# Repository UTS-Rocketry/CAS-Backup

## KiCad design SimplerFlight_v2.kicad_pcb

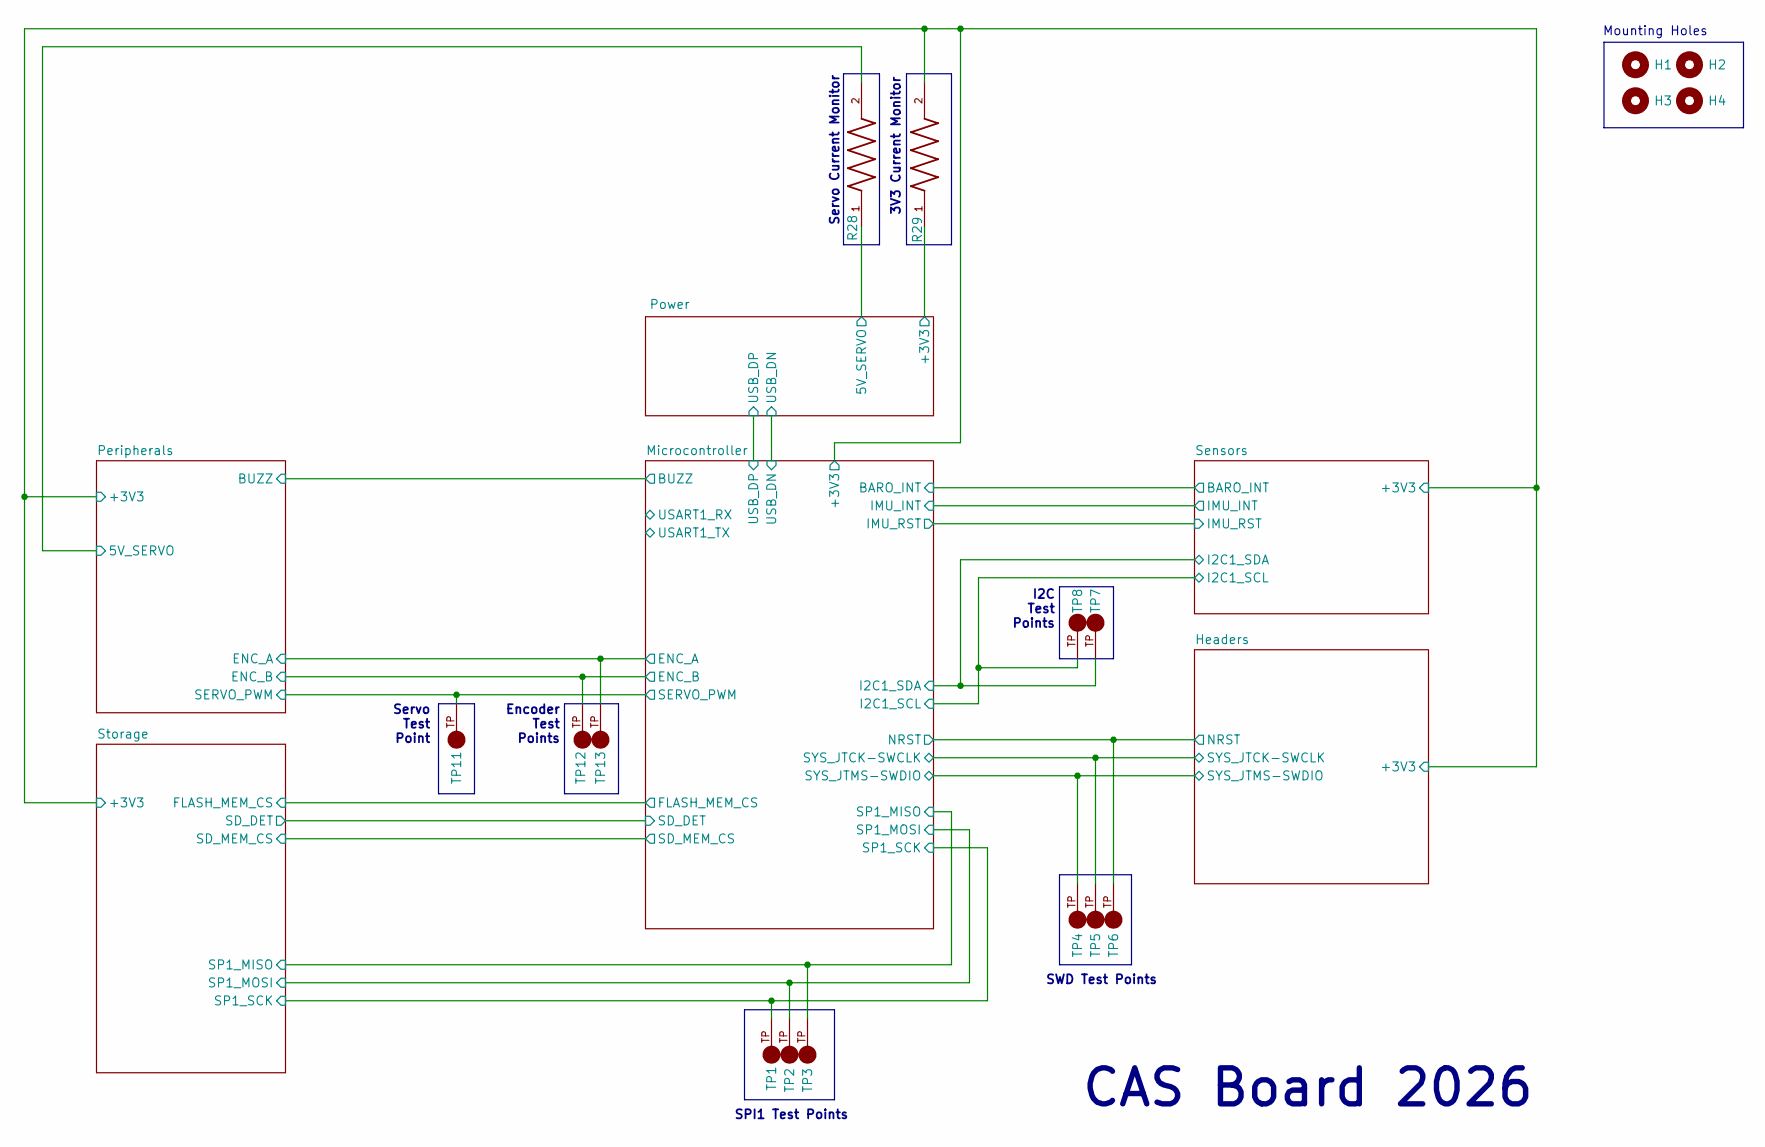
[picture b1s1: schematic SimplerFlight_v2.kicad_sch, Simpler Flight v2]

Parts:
H1, H2, H3, H4: MountingHole; MountingHole_3.2mm_M3
R28, R29: CSRN2512FKR500; RESC6331X70N
TP1, TP2, TP3, TP4, TP5, TP6, TP7, TP8, TP11, TP12, TP13: 5016; KEYSTONE_5016; PARTREV D

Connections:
/Headers/+3V3: R29.2; also elsewhere on the board
/Microcontroller/12C1_SCL: TP8.TP; also elsewhere on the board
/Microcontroller/12C1_SDA: TP7.TP; also elsewhere on the board
/Microcontroller/SPI1_MISO: TP3.TP; also elsewhere on the board
/Microcontroller/SPI1_MOSI: TP2.TP; also elsewhere on the board
/Microcontroller/SPI1_SCK: TP1.TP; also elsewhere on the board
/Peripherals/5V_SERVO: R28.2; also elsewhere on the board
/Power/3V3: R29.1; also elsewhere on the board
/Power/5V_SERVO: R28.1; also elsewhere on the board

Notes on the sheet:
SWD Test Points
3V3 Current Monitor
I2C Test Points
Servo Test Point
SPI1 Test Points
Servo Current Monitor
CAS Board 2026
Mounting Holes
Encoder Test Points

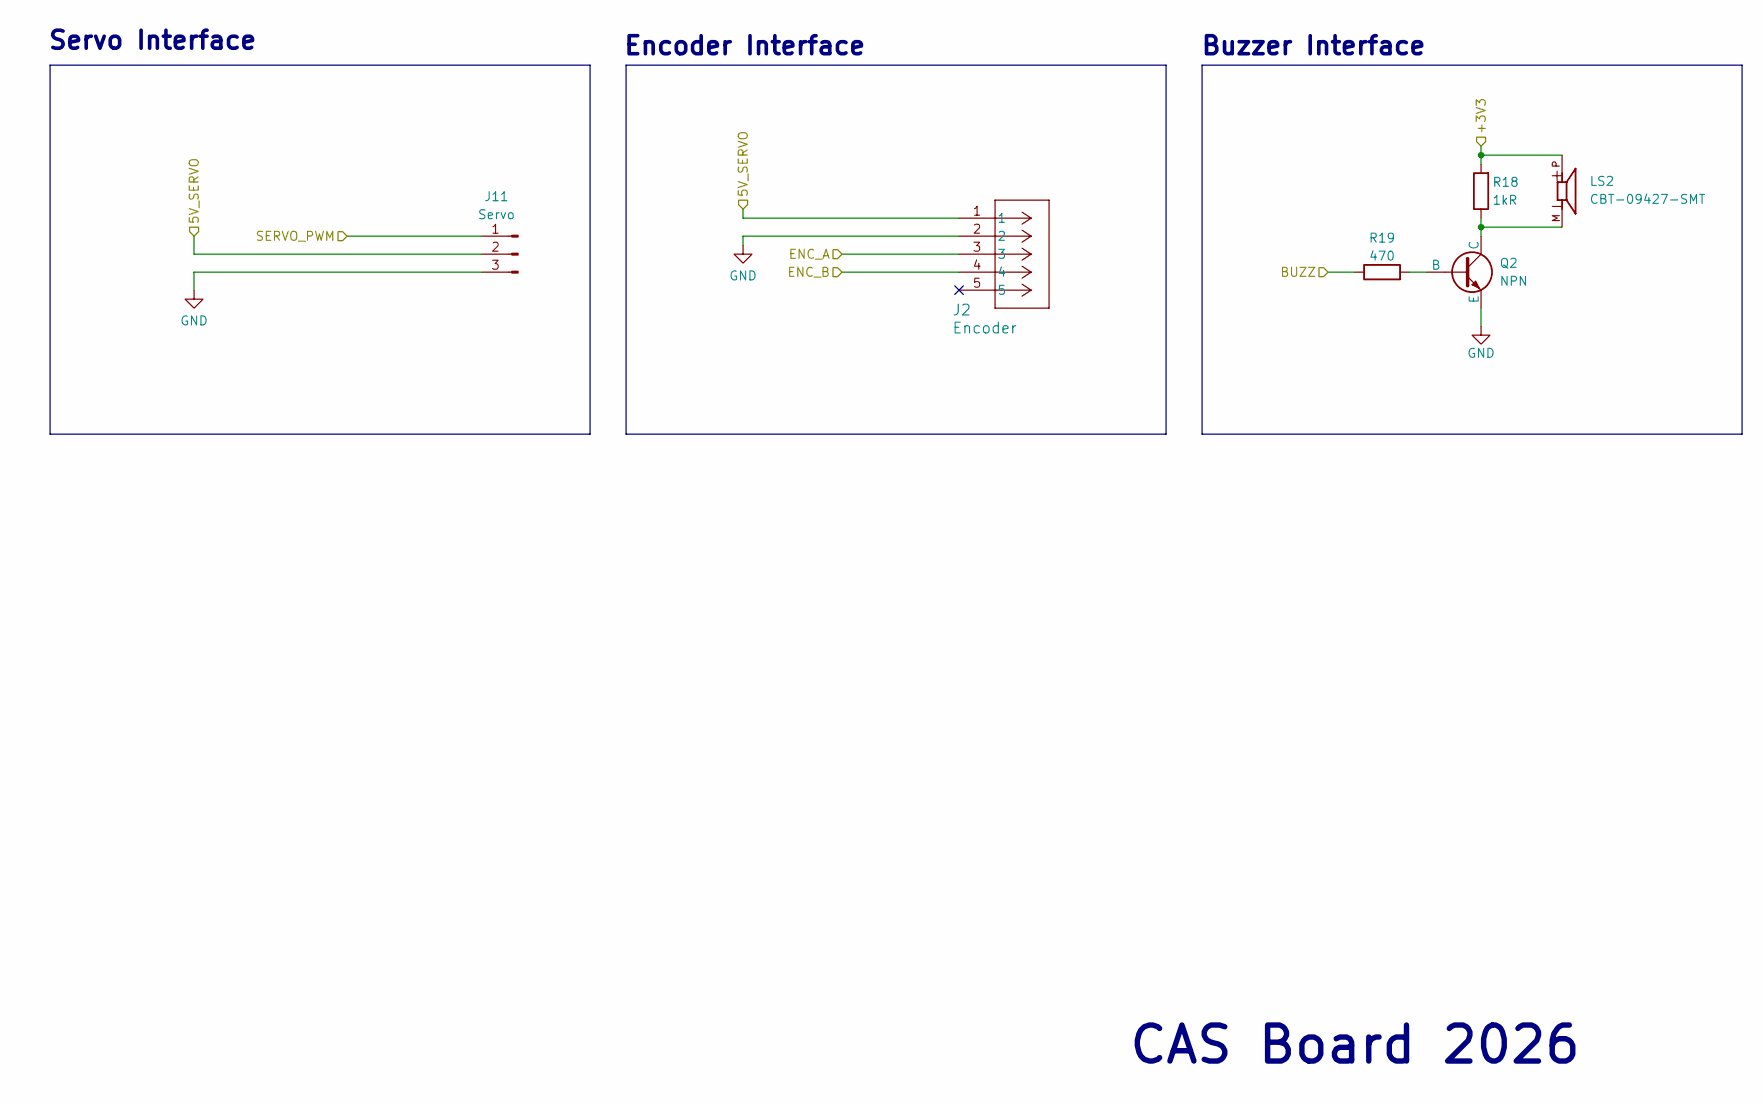
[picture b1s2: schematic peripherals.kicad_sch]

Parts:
J2: Encoder; CONN_S05B-PASK-2_JST
J11: Servo; PinHeader_1x03_P2.54mm_Vertical
LS2: CBT-09427-SMT; CUI_CBT-09427-SMT
Q2: NPN; SSOT3_3X1P5_ONS
R18: 1kR; R_0805_2012Metric_Pad1.20x1.40mm_HandSolder
R19: 470; R_0805_2012Metric_Pad1.20x1.40mm_HandSolder

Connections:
/Headers/+3V3: LS2.P, R18.2; also elsewhere on the board
/Microcontroller/BUZZ: R19.1; also elsewhere on the board
/Microcontroller/ENC_A: J2.3; also elsewhere on the board
/Microcontroller/ENC_B: J2.4; also elsewhere on the board
/Microcontroller/SERVO_PWM: J11.1; also elsewhere on the board
/Peripherals/5V_SERVO: J2.1, J11.2; also elsewhere on the board
GND: J2.2, J11.3, Q2.3 (E); also elsewhere on the board
unnamed: Q2.2 (B), R19.2
unnamed: LS2.M, Q2.1 (C), R18.1

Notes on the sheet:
Encoder Interface
CAS Board 2026
Servo Interface
Buzzer Interface

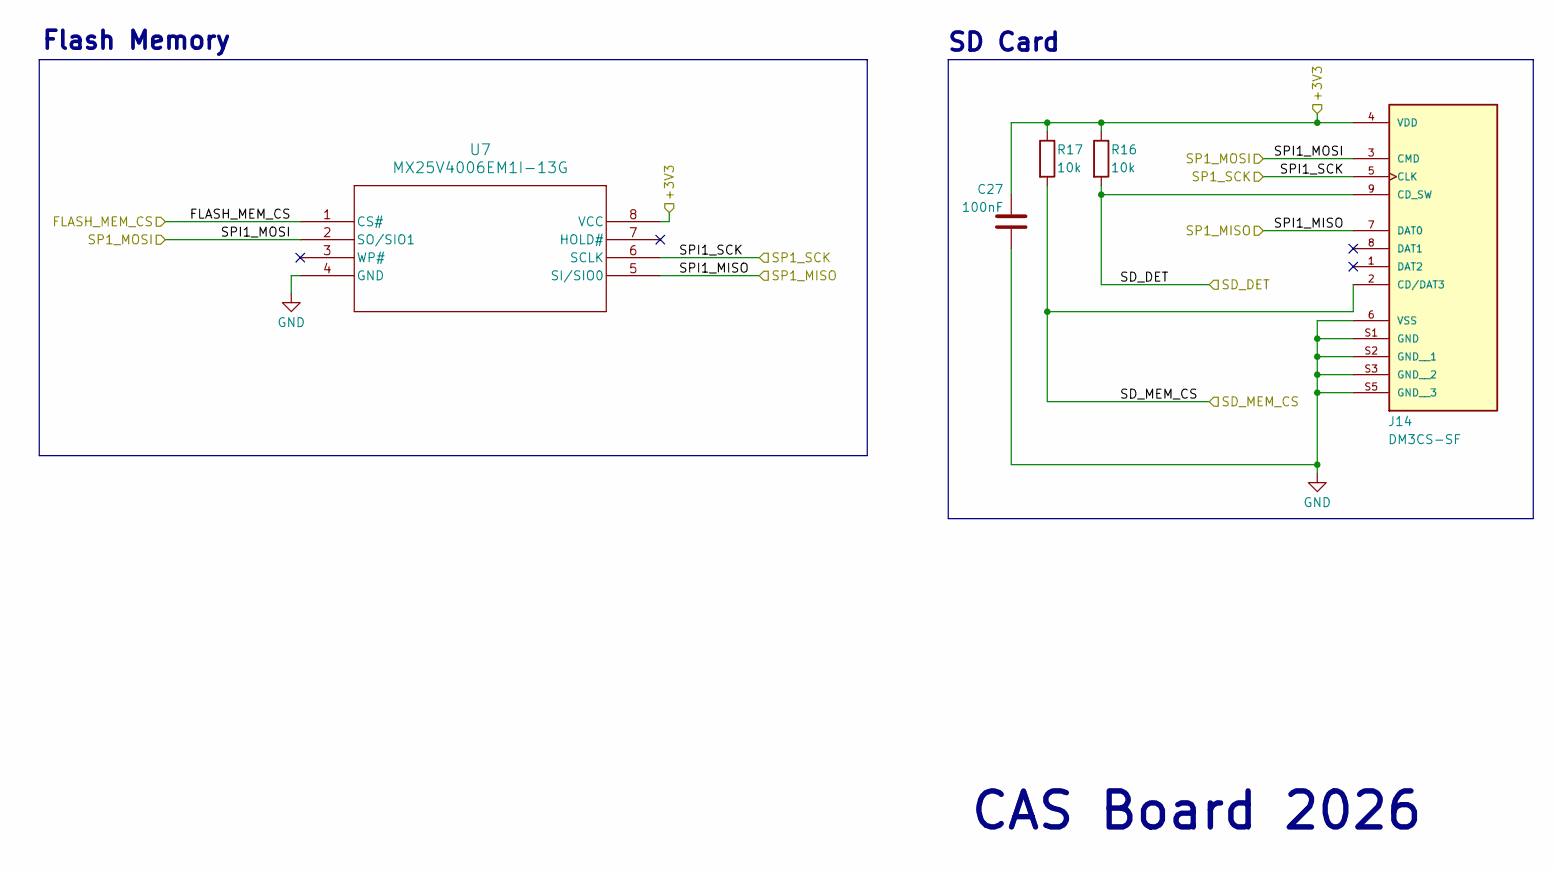
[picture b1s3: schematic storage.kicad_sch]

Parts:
C27: 100nF; C_0805_2012Metric_Pad1.18x1.45mm_HandSolder
J14: DM3CS-SF; HRS_DM3CS-SF; PARTREV n/a
R16, R17: 10k; R_0805_2012Metric_Pad1.20x1.40mm_HandSolder
U7: MX25V4006EM1I-13G; SOP8_150_MAC

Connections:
/Headers/+3V3: C27.1, J14.4 (VDD), R16.1, R17.1, U7.8 (VCC); also elsewhere on the board
/Microcontroller/FLASH_MEM_CS: U7.1 (CS#); also elsewhere on the board
/Microcontroller/SD_DET: J14.9 (CD_SW), R16.2; also elsewhere on the board
/Microcontroller/SD_MEM_CS: J14.2 (CD/DAT3), R17.2; also elsewhere on the board
/Microcontroller/SPI1_MISO: J14.7 (DAT0), U7.5 (SI/SIO0); also elsewhere on the board
/Microcontroller/SPI1_MOSI: J14.3 (CMD), U7.2 (SO/SIO1); also elsewhere on the board
/Microcontroller/SPI1_SCK: J14.5 (CLK), U7.6 (SCLK); also elsewhere on the board
GND: C27.2, J14.6 (VSS), J14.S1 (GND), J14.S2 (GND__1), J14.S3 (GND__2), J14.S5 (GND__3), U7.4 (GND); also elsewhere on the board

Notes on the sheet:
Flash Memory
SD Card
CAS Board 2026

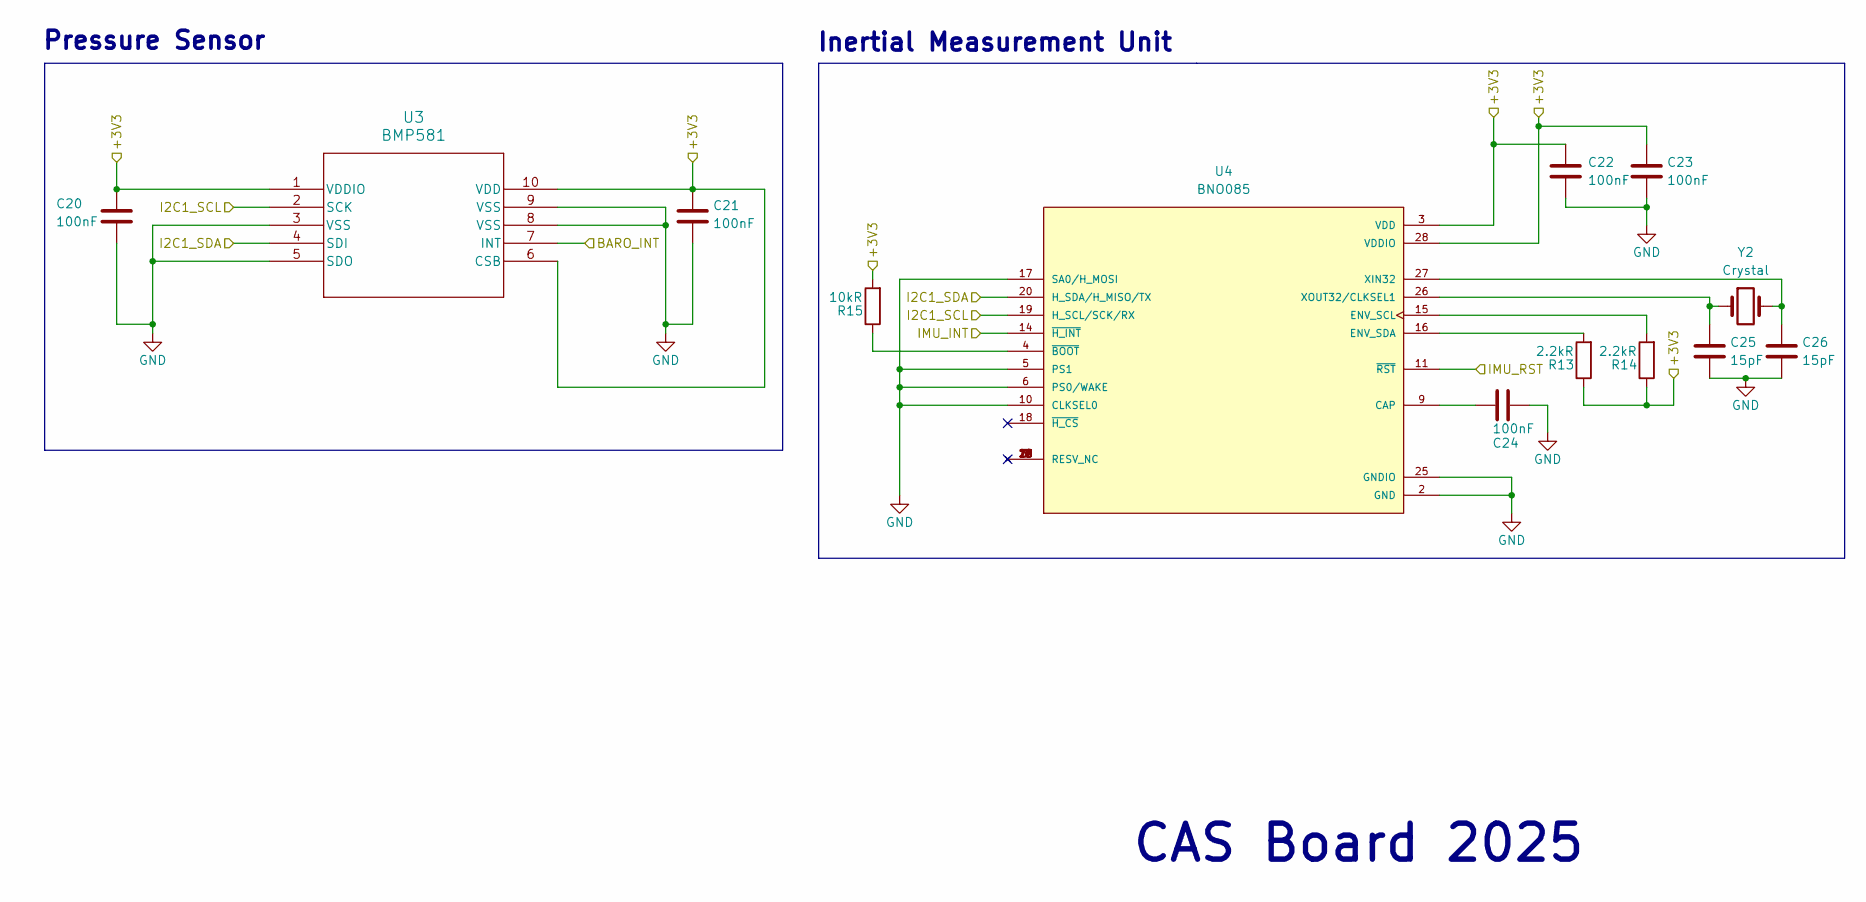
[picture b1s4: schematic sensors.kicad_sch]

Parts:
C20, C21, C22, C23, C24: 100nF; C_0805_2012Metric
C25, C26: 15pF; C_0805_2012Metric
R13, R14: 2.2kR; R_0805_2012Metric_Pad1.20x1.40mm_HandSolder
R15: 10kR; R_0805_2012Metric_Pad1.20x1.40mm_HandSolder
U3: BMP581; QFN10_BMP581_BOS
U4: BNO085; IC_BNO085; PARTREV v1.17
Y2: Crystal; Crystal_SMD_0603-2Pin_6.0x3.5mm_HandSoldering

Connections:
/Headers/+3V3: C20.1, C21.1, C22.1, C23.1, R13.1, R14.1, R15.2, U3.1 (VDDIO), U3.6 (CSB), U3.10 (VDD), U4.3 (VDD), U4.28 (VDDIO); also elsewhere on the board
/Microcontroller/12C1_SCL: U3.2 (SCK), U4.19 (H_SCL/SCK/RX); also elsewhere on the board
/Microcontroller/12C1_SDA: U3.4 (SDI), U4.20 (H_SDA/H_MISO/TX); also elsewhere on the board
/Microcontroller/BARO_INT: U3.7 (INT); also elsewhere on the board
/Microcontroller/IMU_INT: U4.14 (~H_INT); also elsewhere on the board
/Microcontroller/IMU_RST: U4.11 (~RST); also elsewhere on the board
GND: C20.2, C21.2, C22.2, C23.2, C24.1, C25.2, C26.2, U3.3 (VSS), U3.5 (SDO), U3.8 (VSS), U3.9 (VSS), U4.2 (GND), U4.5 (PS1), U4.6 (PS0/WAKE), U4.10 (CLKSEL0), U4.17 (SA0/H_MOSI), U4.25 (GNDIO); also elsewhere on the board
unnamed: C24.2, U4.9 (CAP)
unnamed: R14.2, U4.15 (ENV_SCL)
unnamed: R13.2, U4.16 (ENV_SDA)
unnamed: C26.1, U4.27 (XIN32), Y2.2
unnamed: C25.1, U4.26 (XOUT32/CLKSEL1), Y2.1
unnamed: R15.1, U4.4 (~BOOT)

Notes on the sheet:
CAS Board 2025
Inertial Measurement Unit
Pressure Sensor

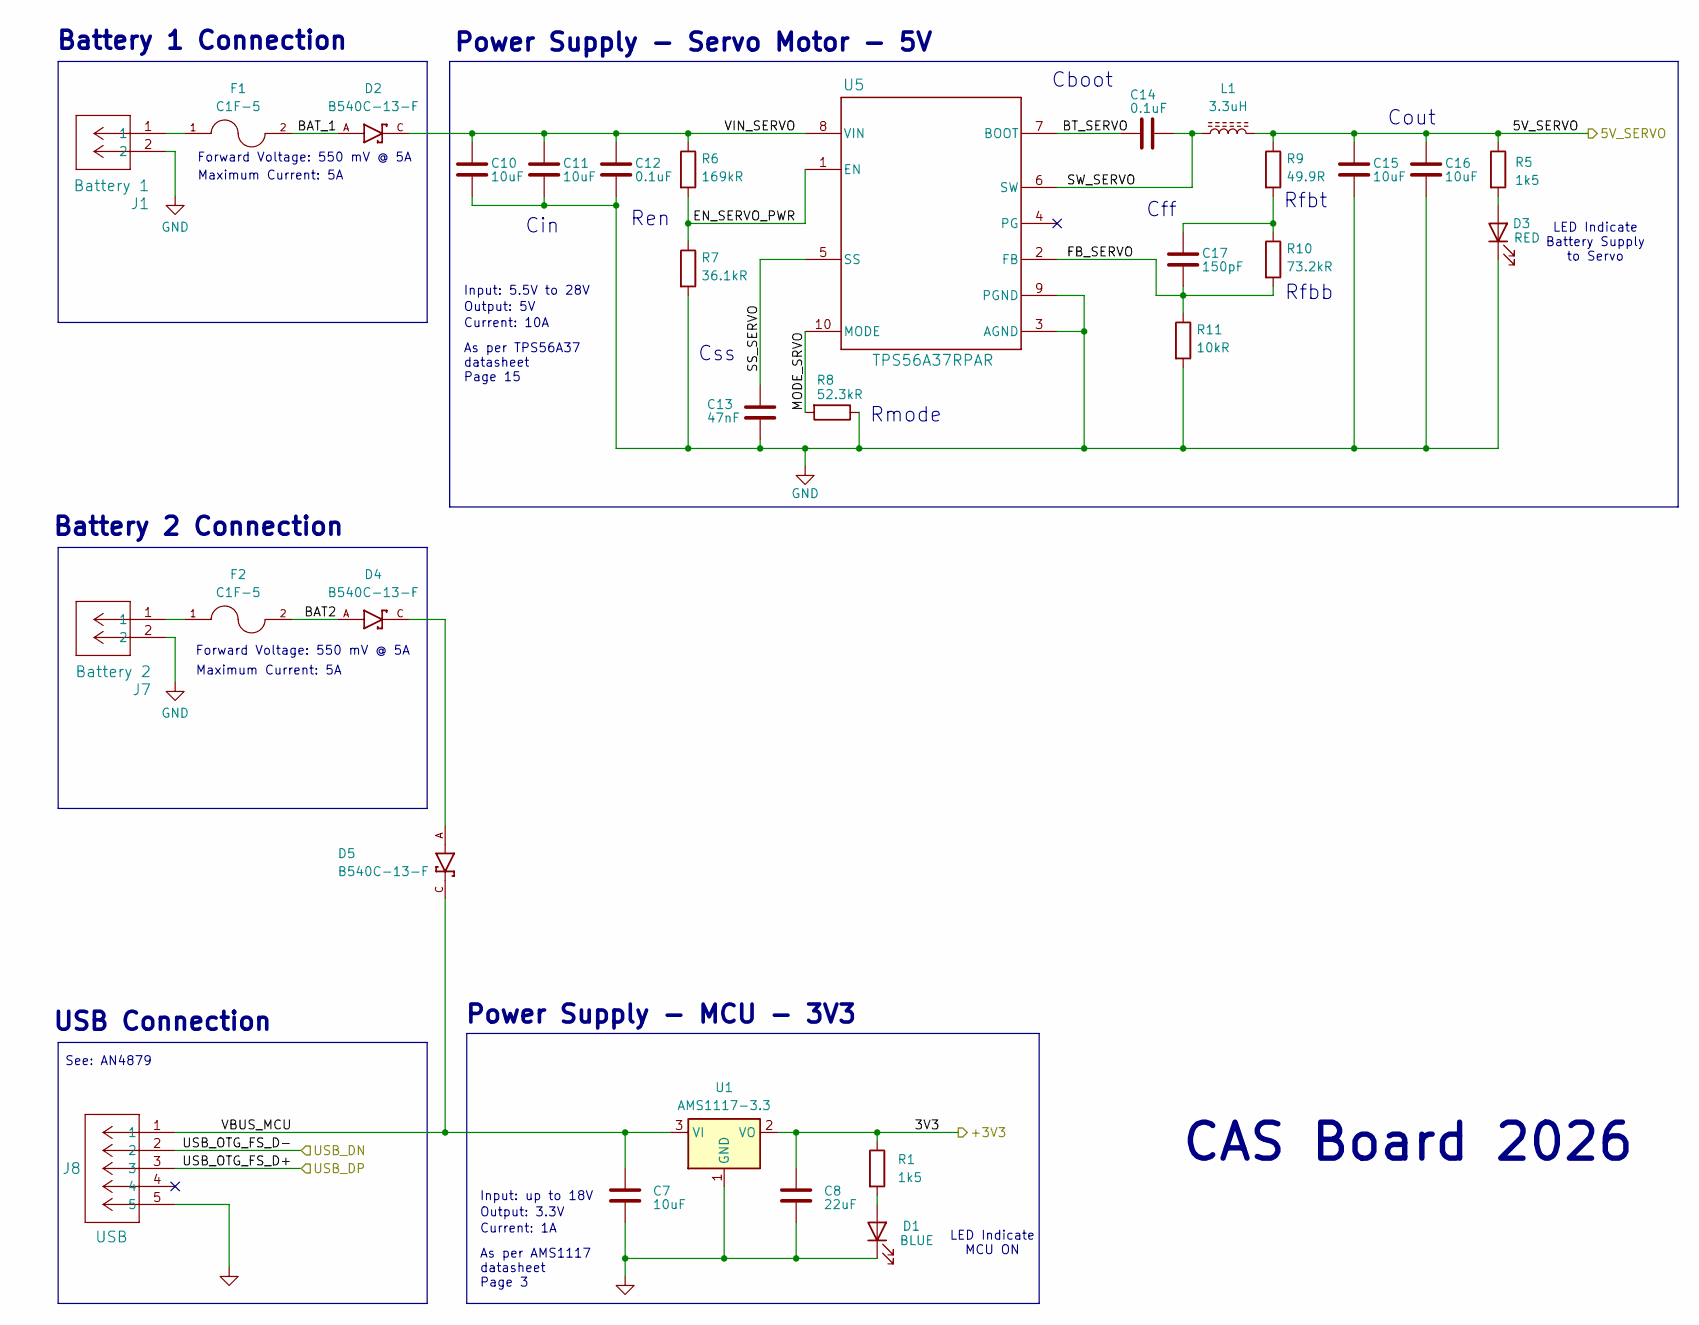
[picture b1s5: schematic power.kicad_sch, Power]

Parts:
C7, C10, C11, C15, C16: 10uF; C_0805_2012Metric
C8: 22uF; C_0805_2012Metric
C12, C14: 0.1uF; C_0805_2012Metric
C13: 47nF; C_0805_2012Metric
C17: 150pF; C_0805_2012Metric
D1: BLUE; LED_0805_2012Metric
D2, D4, D5: B540C-13-F; DIOM6959X245N; PARTREV V1.0
D3: RED; LED_0805_2012Metric
F1, F2: C1F-5; FUSC3215X83N; PARTREV Jan2019
J1: Battery 1; CONN_SD-5566-002_02_MOL
J7: Battery 2; CONN_SD-5566-002_02_MOL
J8: USB; CON00317_5_MOL
L1: 3.3uH; L_0805_2012Metric_Pad1.05x1.20mm_HandSolder
R1, R5: 1k5; C_0805_2012Metric
R6: 169kR; C_0805_2012Metric
R7: 36.1kR; C_0805_2012Metric
R8: 52.3kR; C_0805_2012Metric
R9: 49.9R; C_0805_2012Metric
R10: 73.2kR; C_0805_2012Metric
R11: 10kR; C_0805_2012Metric
U1: AMS1117-3.3; SOT-223-3_TabPin2
U5: TPS56A37RPAR; RPA0010A-MFG

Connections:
/Microcontroller/USB_OTG_FS_D+: J8.3; also elsewhere on the board
/Microcontroller/USB_OTG_FS_D-: J8.2; also elsewhere on the board
/Power/3V3: C8.1, R1.1, U1.2 (VO); also elsewhere on the board
/Power/5V_SERVO: C15.1, C16.1, L1.2, R5.1, R9.1; also elsewhere on the board
/Power/BAT2: D4.A, F2.2
/Power/BAT_1: D2.A, F1.2
/Power/BT_SERVO: C14.1, U5.7 (BOOT)
/Power/EN_SERVO_PWR: R6.2, R7.1, U5.1 (EN)
/Power/FB_SERVO: C17.2, R10.2, R11.1, U5.2 (FB)
/Power/MODE_SRVO: R8.2, U5.10 (MODE)
/Power/SS_SERVO: C13.1, U5.5 (SS)
/Power/SW_SERVO: C14.2, L1.1, U5.6 (SW)
/Power/VBUS_MCU: C7.1, D5.C, J8.1, U1.3 (VI)
/Power/VIN_SERVO: C10.1, C11.1, C12.1, D2.C, R6.1, U5.8 (VIN)
GND: C7.2, C8.2, C10.2, C11.2, C12.2, C13.2, C15.2, C16.2, D1.1 (K), D3.1 (K), J1.2, J7.2, J8.5, R7.2, R8.1, R11.2, U1.1 (GND), U5.3 (AGND), U5.9 (PGND); also elsewhere on the board
unnamed: C17.1, R9.2, R10.1
unnamed: D1.2 (A), R1.2
unnamed: D3.2 (A), R5.2
unnamed: D4.C, D5.A
unnamed: F1.1, J1.1
unnamed: F2.1, J7.1

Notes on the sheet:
Cff
USB Connection
Output: 5V
Current: 10A
Battery 1 Connection
Maximum Current: 5A
LED Indicate MCU ON
Rfbb
See: AN4879
Forward Voltage: 550 mV @ 5A
Output: 3.3V
Power Supply - Servo Motor - 5V
Input: 5.5V to 28V
CAS Board 2026
Current: 1A
Ren
Cboot
LED Indicate Battery Supply to Servo
As per TPS56A37 datasheet Page 15
Cin
Css
As per AMS1117 datasheet Page 3
Power Supply - MCU - 3V3
Cout
Input: up to 18V
Rfbt
Battery 2 Connection
Rmode

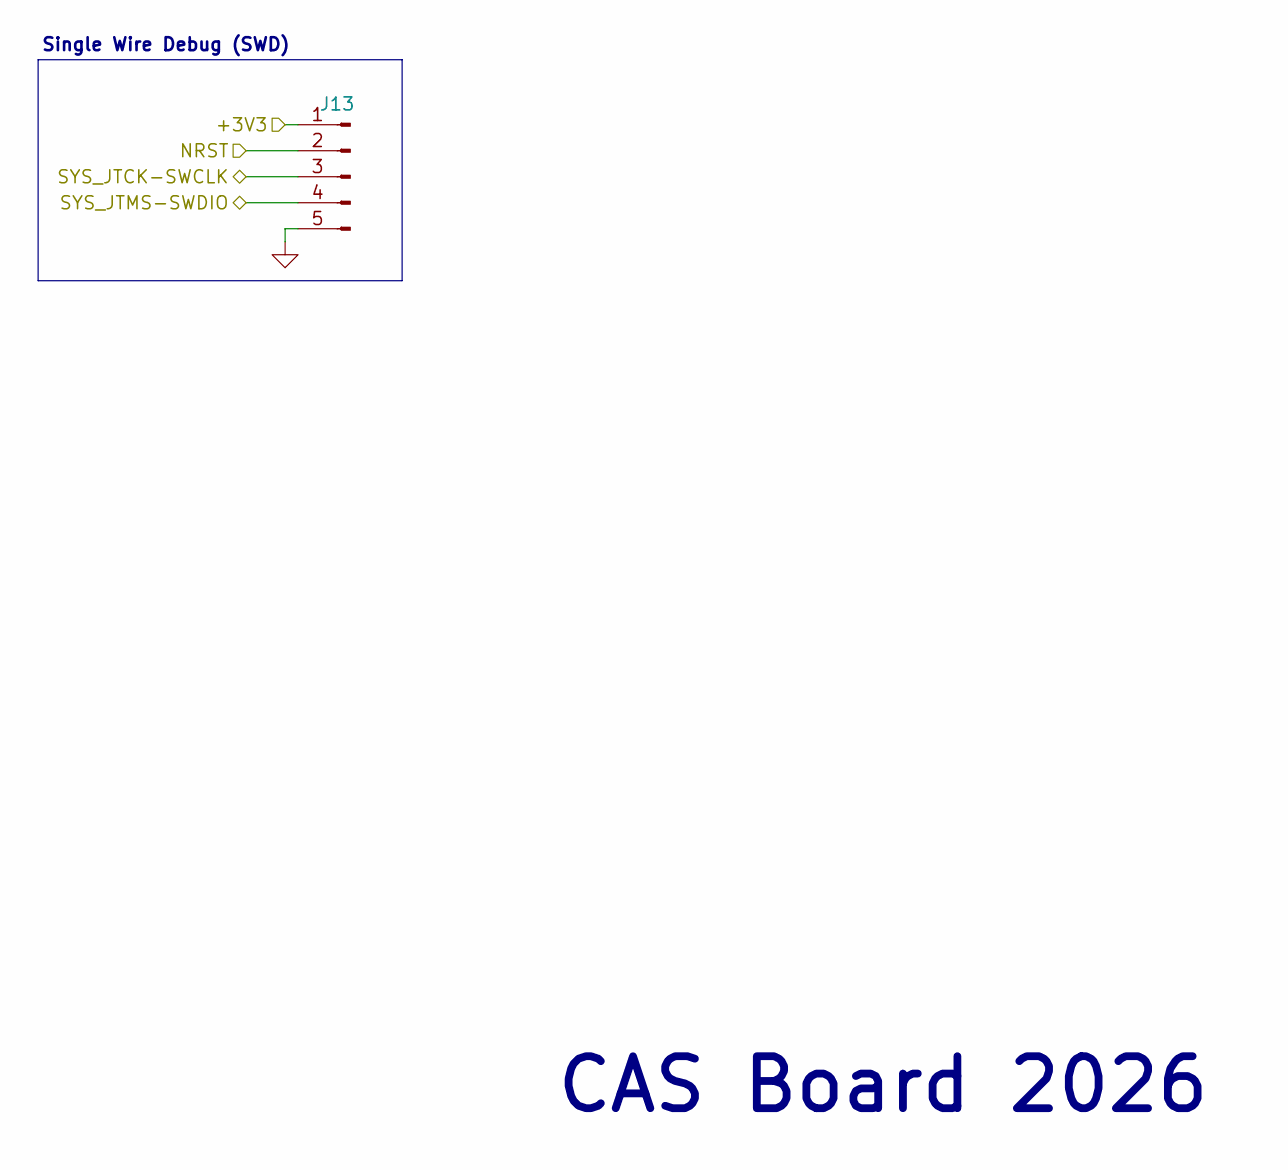
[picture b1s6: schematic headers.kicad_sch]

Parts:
J13: SWD Header; PinHeader_1x05_P2.54mm_Vertical

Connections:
/Headers/+3V3: J13.1; also elsewhere on the board
/Microcontroller/SYS_JTCK-SWCLK: J13.3; also elsewhere on the board
/Microcontroller/SYS_JTMS-SWDIO: J13.4; also elsewhere on the board
GND: J13.5; also elsewhere on the board
NRST: J13.2; also elsewhere on the board

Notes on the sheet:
CAS Board 2026
Single Wire Debug (SWD)

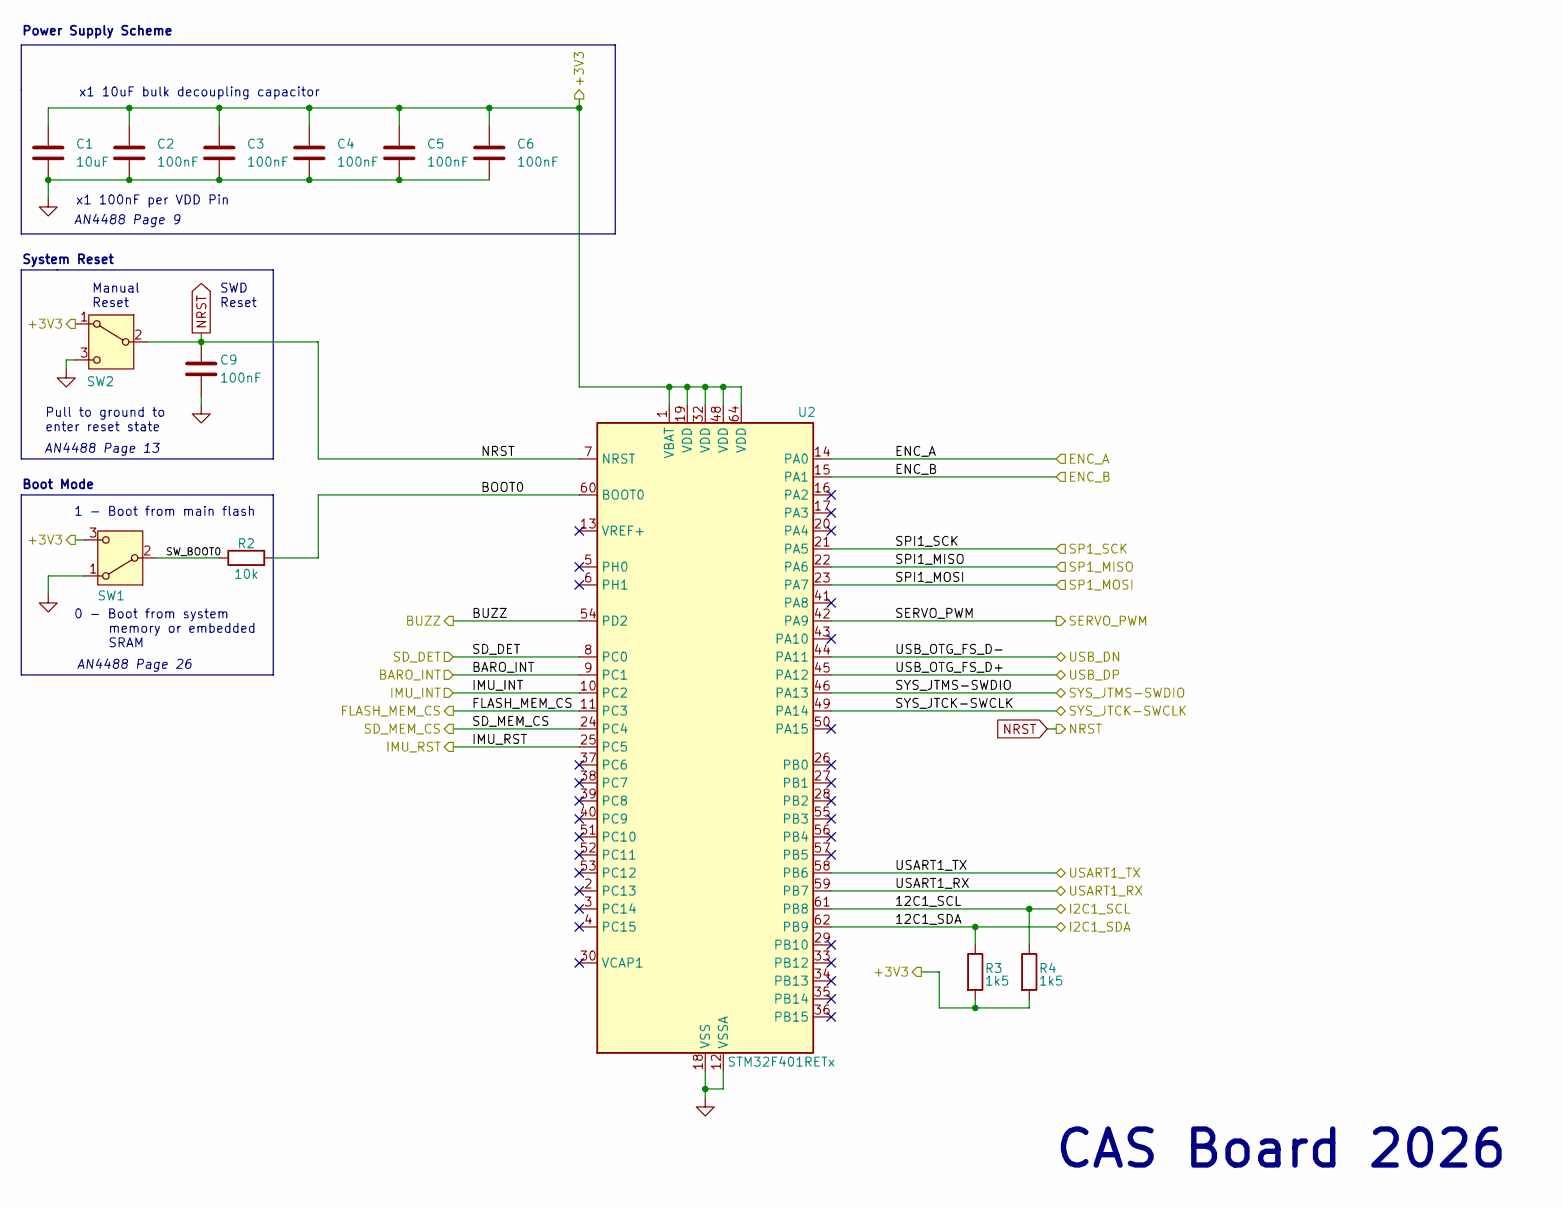
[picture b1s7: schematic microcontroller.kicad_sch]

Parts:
C1: 10uF; C_0805_2012Metric
C2, C3, C4, C5, C6, C9: 100nF; C_0805_2012Metric
R2: 10k; C_0805_2012Metric
R3, R4: 1k5; C_0805_2012Metric
SW1: Boot Switch; SW_SPDT_PCM12
SW2: System Reset; SW_SPDT_PCM12
U2: STM32F401RETx; LQFP-64_10x10mm_P0.5mm

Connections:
/Headers/+3V3: C1.1, C2.1, C3.1, C4.1, C5.1, C6.1, R3.2, R4.2, SW1.3 (C), SW2.1 (A), U2.1 (VBAT), U2.19 (VDD), U2.32 (VDD), U2.48 (VDD), U2.64 (VDD); also elsewhere on the board
/Microcontroller/12C1_SCL: R4.1, U2.61 (PB8); also elsewhere on the board
/Microcontroller/12C1_SDA: R3.1, U2.62 (PB9); also elsewhere on the board
/Microcontroller/BARO_INT: U2.9 (PC1); also elsewhere on the board
/Microcontroller/BOOT0: R2.2, U2.60 (BOOT0)
/Microcontroller/BUZZ: U2.54 (PD2); also elsewhere on the board
/Microcontroller/ENC_A: U2.14 (PA0); also elsewhere on the board
/Microcontroller/ENC_B: U2.15 (PA1); also elsewhere on the board
/Microcontroller/FLASH_MEM_CS: U2.11 (PC3); also elsewhere on the board
/Microcontroller/IMU_INT: U2.10 (PC2); also elsewhere on the board
/Microcontroller/IMU_RST: U2.25 (PC5); also elsewhere on the board
/Microcontroller/SD_DET: U2.8 (PC0); also elsewhere on the board
/Microcontroller/SD_MEM_CS: U2.24 (PC4); also elsewhere on the board
/Microcontroller/SERVO_PWM: U2.42 (PA9); also elsewhere on the board
/Microcontroller/SPI1_MISO: U2.22 (PA6); also elsewhere on the board
/Microcontroller/SPI1_MOSI: U2.23 (PA7); also elsewhere on the board
/Microcontroller/SPI1_SCK: U2.21 (PA5); also elsewhere on the board
/Microcontroller/SW_BOOT0: R2.1, SW1.2 (B)
/Microcontroller/SYS_JTCK-SWCLK: U2.49 (PA14); also elsewhere on the board
/Microcontroller/SYS_JTMS-SWDIO: U2.46 (PA13); also elsewhere on the board
/Microcontroller/USART1_RX: U2.59 (PB7)
/Microcontroller/USART1_TX: U2.58 (PB6)
/Microcontroller/USB_OTG_FS_D+: U2.45 (PA12); also elsewhere on the board
/Microcontroller/USB_OTG_FS_D-: U2.44 (PA11); also elsewhere on the board
GND: C1.2, C2.2, C3.2, C4.2, C5.2, C6.2, C9.2, SW1.1 (A), SW2.3 (C), U2.12 (VSSA), U2.18 (VSS), U2.31 (VSS), U2.47 (VSS), U2.63 (VSS); also elsewhere on the board
NRST: C9.1, SW2.2 (B), U2.7 (NRST); also elsewhere on the board

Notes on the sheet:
1 - Boot from main flash
SWD Reset
x1 100nF per VDD Pin
AN4488 Page 26
CAS Board 2026
0 - Boot from system memory or embedded SRAM
x1 10uF bulk decoupling capacitor
Power Supply Scheme
AN4488 Page 9
Manual Reset
System Reset
AN4488 Page 13
Boot Mode
Pull to ground to enter reset state

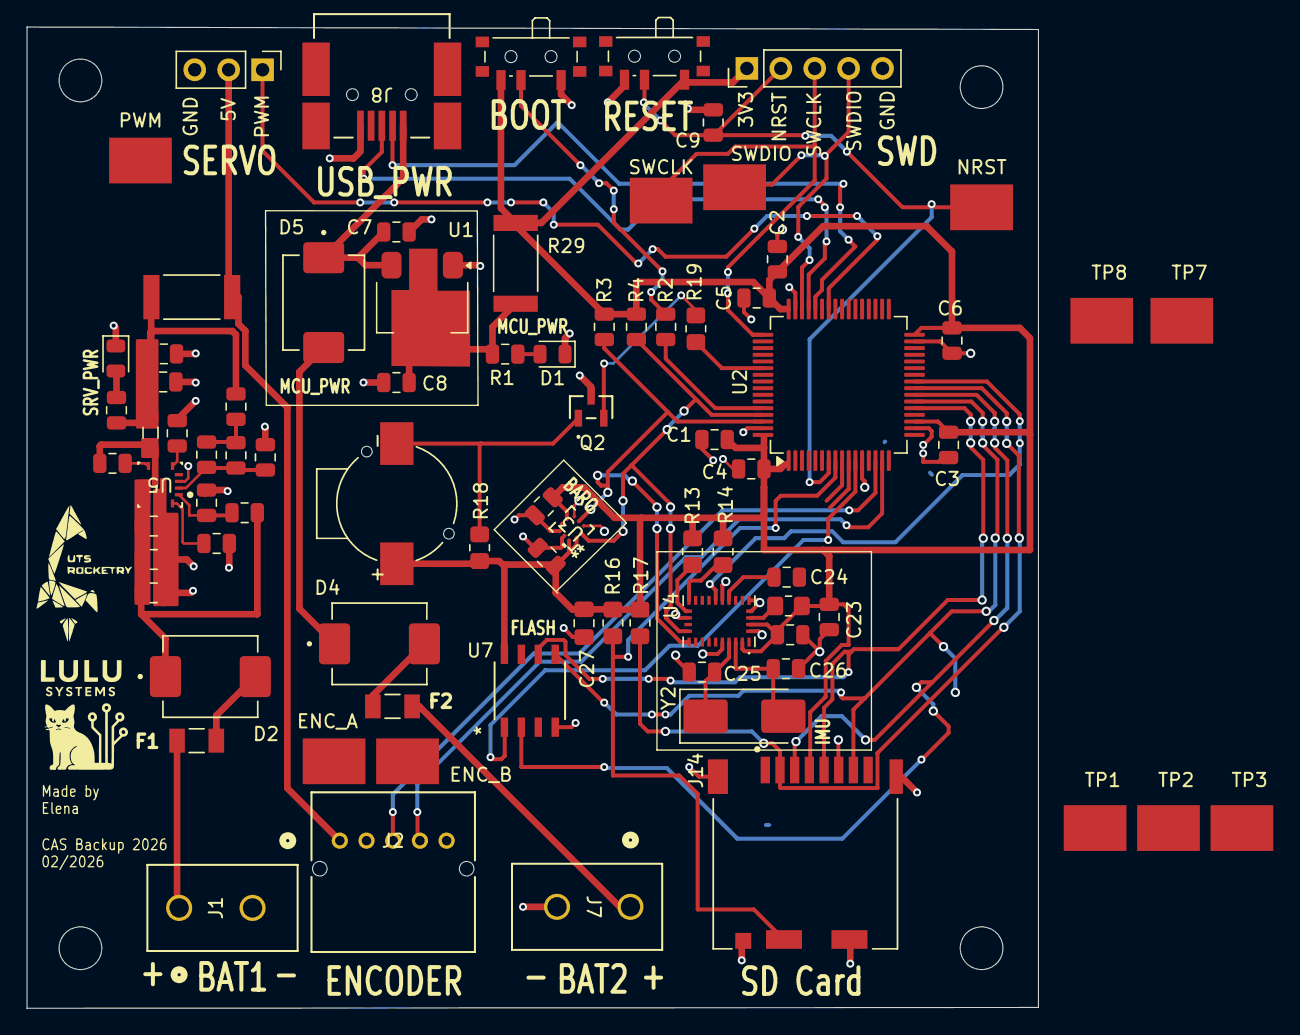
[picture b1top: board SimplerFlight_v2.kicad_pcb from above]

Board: 2 copper layers, 75.8 x 73.5 mm, 86 parts (0 on the bottom side), 51 nets.

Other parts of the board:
ENC_A: 5016; KEYSTONE_5016
ENC_B: 5016; KEYSTONE_5016
NRST: 5016; KEYSTONE_5016
PWM: 5016; KEYSTONE_5016
SWCLK: 5016; KEYSTONE_5016
SWDIO: 5016; KEYSTONE_5016

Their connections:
/Microcontroller/ENC_A: ENC_A.TP; also elsewhere on the board
/Microcontroller/ENC_B: ENC_B.TP; also elsewhere on the board
/Microcontroller/SERVO_PWM: PWM.TP; also elsewhere on the board
/Microcontroller/SYS_JTCK-SWCLK: SWCLK.TP; also elsewhere on the board
/Microcontroller/SYS_JTMS-SWDIO: SWDIO.TP; also elsewhere on the board
NRST: NRST.TP; also elsewhere on the board

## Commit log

2026-02-01 remove camera power and interface headers and pins from schematic and PCB
2026-02-01 remove unused pins from mcu schematic and root schematic
2026-02-02 remove redundant current sensing
2026-02-07 make pcb footprint smaller
2026-02-07 temp todo list
2026-02-07 update todo and add pic
